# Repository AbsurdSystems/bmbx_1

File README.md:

# bmbx_1
A 65c02 homebrew computer board using a PLD glue logic

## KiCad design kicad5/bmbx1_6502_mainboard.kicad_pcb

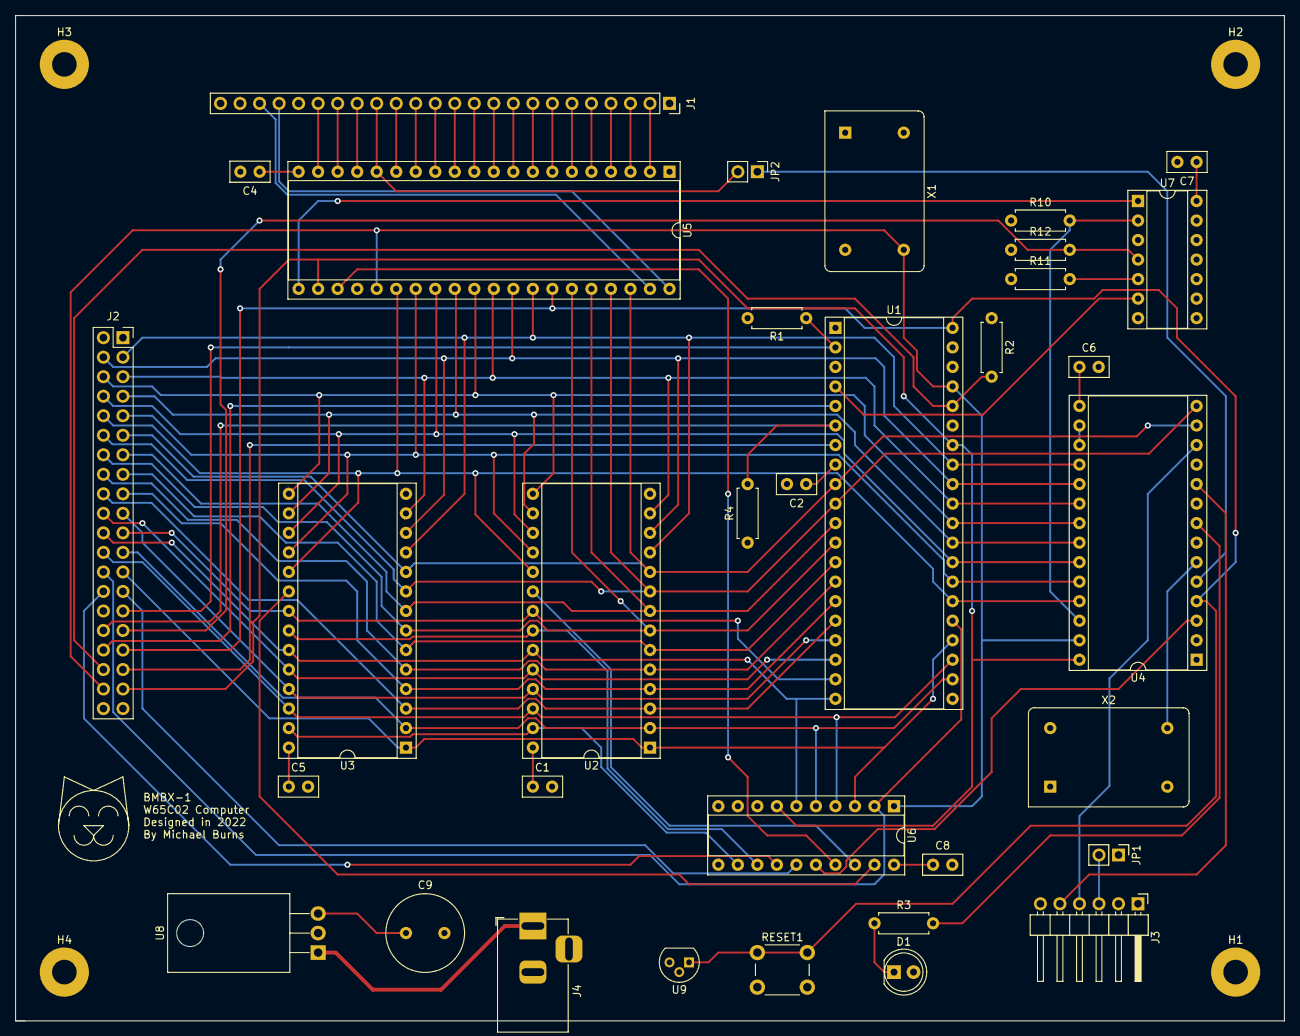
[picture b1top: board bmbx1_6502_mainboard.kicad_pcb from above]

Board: 4 copper layers, 165.1 x 130.8 mm, 38 parts (0 on the bottom side), 75 nets.

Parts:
C1, C2, C4, C5, C6, C7, C8: 100uF; C_Disc_D5.0mm_W2.5mm_P2.50mm
C9: 470uF; C_Radial_D10.0mm_H16.0mm_P5.00mm
D1: LED; LED_D5.0mm_Clear
H1, H2, H3, H4: MountingHole_Pad; MountingHole_3.2mm_M3_Pad
J1: Conn_01x24; PinSocket_1x24_P2.54mm_Vertical
J2: Conn_02x20_Odd_Even; PinSocket_2x20_P2.54mm_Vertical
J3: Conn_01x06_Female; PinHeader_1x06_P2.54mm_Horizontal
J4: Barrel_Jack; BarrelJack_Horizontal
JP1, JP2: Jumper_2_Open; PinHeader_1x02_P2.54mm_Vertical
R1, R2, R4: 3K; R_Axial_DIN0207_L6.3mm_D2.5mm_P7.62mm_Horizontal
R3: 470; R_Axial_DIN0207_L6.3mm_D2.5mm_P7.62mm_Horizontal
R10, R11, R12: 4.7K; R_Axial_DIN0207_L6.3mm_D2.5mm_P7.62mm_Horizontal
RESET1: SW_Push; SW_PUSH_6mm_H4.3mm
U1: W65C02SxP; DIP-40_W15.24mm_Socket
U2: HM62256BLP; DIP-28_W15.24mm_Socket
U3: 28C256; DIP-28_W15.24mm_Socket
U4: W65C51NxP; DIP-28_W15.24mm_Socket
U5: W65C22SxP; DIP-40_W15.24mm_Socket
U6: GAL16V8; DIP-20_W7.62mm_Socket
U7: 74LS21; DIP-14_W7.62mm_Socket
U8: LM2937xT; TO-220-3_Horizontal_TabDown
U9: DS1813-5+; TO-92
X1: 4 MHz; Oscillator_DIP-14
X2: 1.8432 MHz; Oscillator_DIP-14

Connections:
A0: J2.11, U1.9, U2.10, U3.10, U4.13, U5.38
A1: J2.12, U1.10, U2.9, U3.9, U4.14, U5.37
A2: J2.13, U1.11, U2.8, U3.8, U5.36
A3: J2.14, U1.12, U2.7, U3.7, U5.35
A4: J2.15, U1.13, U2.6, U3.6
A5: J2.16, U1.14, U2.5, U3.5
A6: J2.17, U1.15, U2.4, U3.4
A7: J2.18, U1.16, U2.3, U3.3
A8: J2.19, U1.17, U2.25, U3.25
A9: J2.20, U1.18, U2.24, U3.24
A10: J2.21, U1.19, U2.21, U3.21
A11: J2.22, U1.20, U2.23, U3.23, U6.6
A12: J2.23, U1.22, U2.2, U3.2, U6.5
A13: J2.24, U1.23, U2.26, U3.26, U6.4
A14: J2.25, U1.24, U2.1, U3.1, U6.3
A15: J2.26, U1.25, U6.2
ACIA_IOSEL: U4.3, U6.16
ACIA_IRQ: R10.2, U4.26, U7.2
BAUD_CLK: U4.6, X2.8
BE: J2.36, R2.2, U1.36
CA1: J1.21, U5.40
CA2: J1.22, U5.39
CB1: J1.18, U5.18
CB2: J1.19, U5.19
D0: J2.3, U1.33, U2.11, U3.11, U4.18, U5.33
D1: J2.4, U1.32, U2.12, U3.12, U4.19, U5.32
D2: J2.5, U1.31, U2.13, U3.13, U4.20, U5.31
D3: J2.6, U1.30, U2.15, U3.15, U4.21, U5.30
D4: J2.7, U1.29, U2.16, U3.16, U4.22, U5.29
D5: J2.8, U1.28, U2.17, U3.17, U4.23, U5.28
D6: J2.9, U1.27, U2.18, U3.18, U4.24, U5.27
D7: J2.10, U1.26, U2.19, U3.19, U4.25, U5.26
GND: C1.2, C2.2, C4.2, C5.2, C6.2, C7.2, C8.2, C9.2, H1.1, H2.1, H3.1, H4.1, J1.1, J1.24, J2.2, J2.39, J3.1, J4.2, RESET1.2, U1.21, U2.14, U3.14, U4.1, U4.9, U4.16, U4.17, U5.1, U6.10, U6.11, U7.7, U7.9, U7.10, U7.12, U7.13, U8.2, U9.3, X1.7, X2.7
IO3SEL: J2.27, U6.15
IO3_IRQ: J2.31, R12.2, U7.4
IO4SEL: J2.28, U6.14
IRQ_MAIN: U1.4, U7.6
MLB: J2.34, U1.5
NMI: J2.32, R4.2, U1.6
unnamed: D1.1, R3.1
unnamed: J3.3, JP1.2
unnamed: J4.1, U8.1
unnamed: R3.2, U4.8
unnamed: R11.2, U7.5
PA0: J1.2, U5.2
PA1: J1.3, U5.3
PA2: J1.4, U5.4
PA3: J1.5, U5.5
PA4: J1.6, U5.6
PA5: J1.7, U5.7
PA6: J1.8, U5.8
PA7: J1.9, U5.9
PB0: J1.10, U5.10
PB1: J1.11, U5.11
PB2: J1.12, U5.12
PB3: J1.13, U5.13
PB4: J1.14, U5.14
PB5: J1.15, U5.15
PB6: J1.16, JP2.2, U5.16
PB7: J1.17, U5.17
PHI2: J2.38, U1.37, U4.27, U5.25, U6.1, X1.8
RAM_SEL: U2.20, U6.18
RCLK_OUT: JP2.1, U4.5
RDY: J2.29, R1.1, U1.2
READ_SIG: U2.22, U3.22, U6.13
RES: J2.33, RESET1.1, U1.40, U4.4, U5.34, U9.1
ROM_SEL: U3.20, U6.19
RW: J2.37, U1.34, U4.28, U5.22, U6.7
SYNC: J2.35, U1.7
UART_RX: J3.4, U4.12
UART_TX: J3.5, U4.10
VCC: C1.1, C2.1, C4.1, C5.1, C6.1, C7.1, C8.1, C9.1, D1.2, J1.20, J2.1, J2.40, JP1.1, R1.2, R2.1, R4.1, R10.1, R11.1, R12.1, U1.8, U1.38, U2.28, U3.28, U4.2, U4.15, U5.20, U5.24, U6.20, U7.14, U8.3, U9.2, X1.14, X2.14
VIA_IOSEL: U5.23, U6.17
VIA_IRQ: U5.21, U7.1
WRITE_SIG: U2.27, U3.27, U6.12
